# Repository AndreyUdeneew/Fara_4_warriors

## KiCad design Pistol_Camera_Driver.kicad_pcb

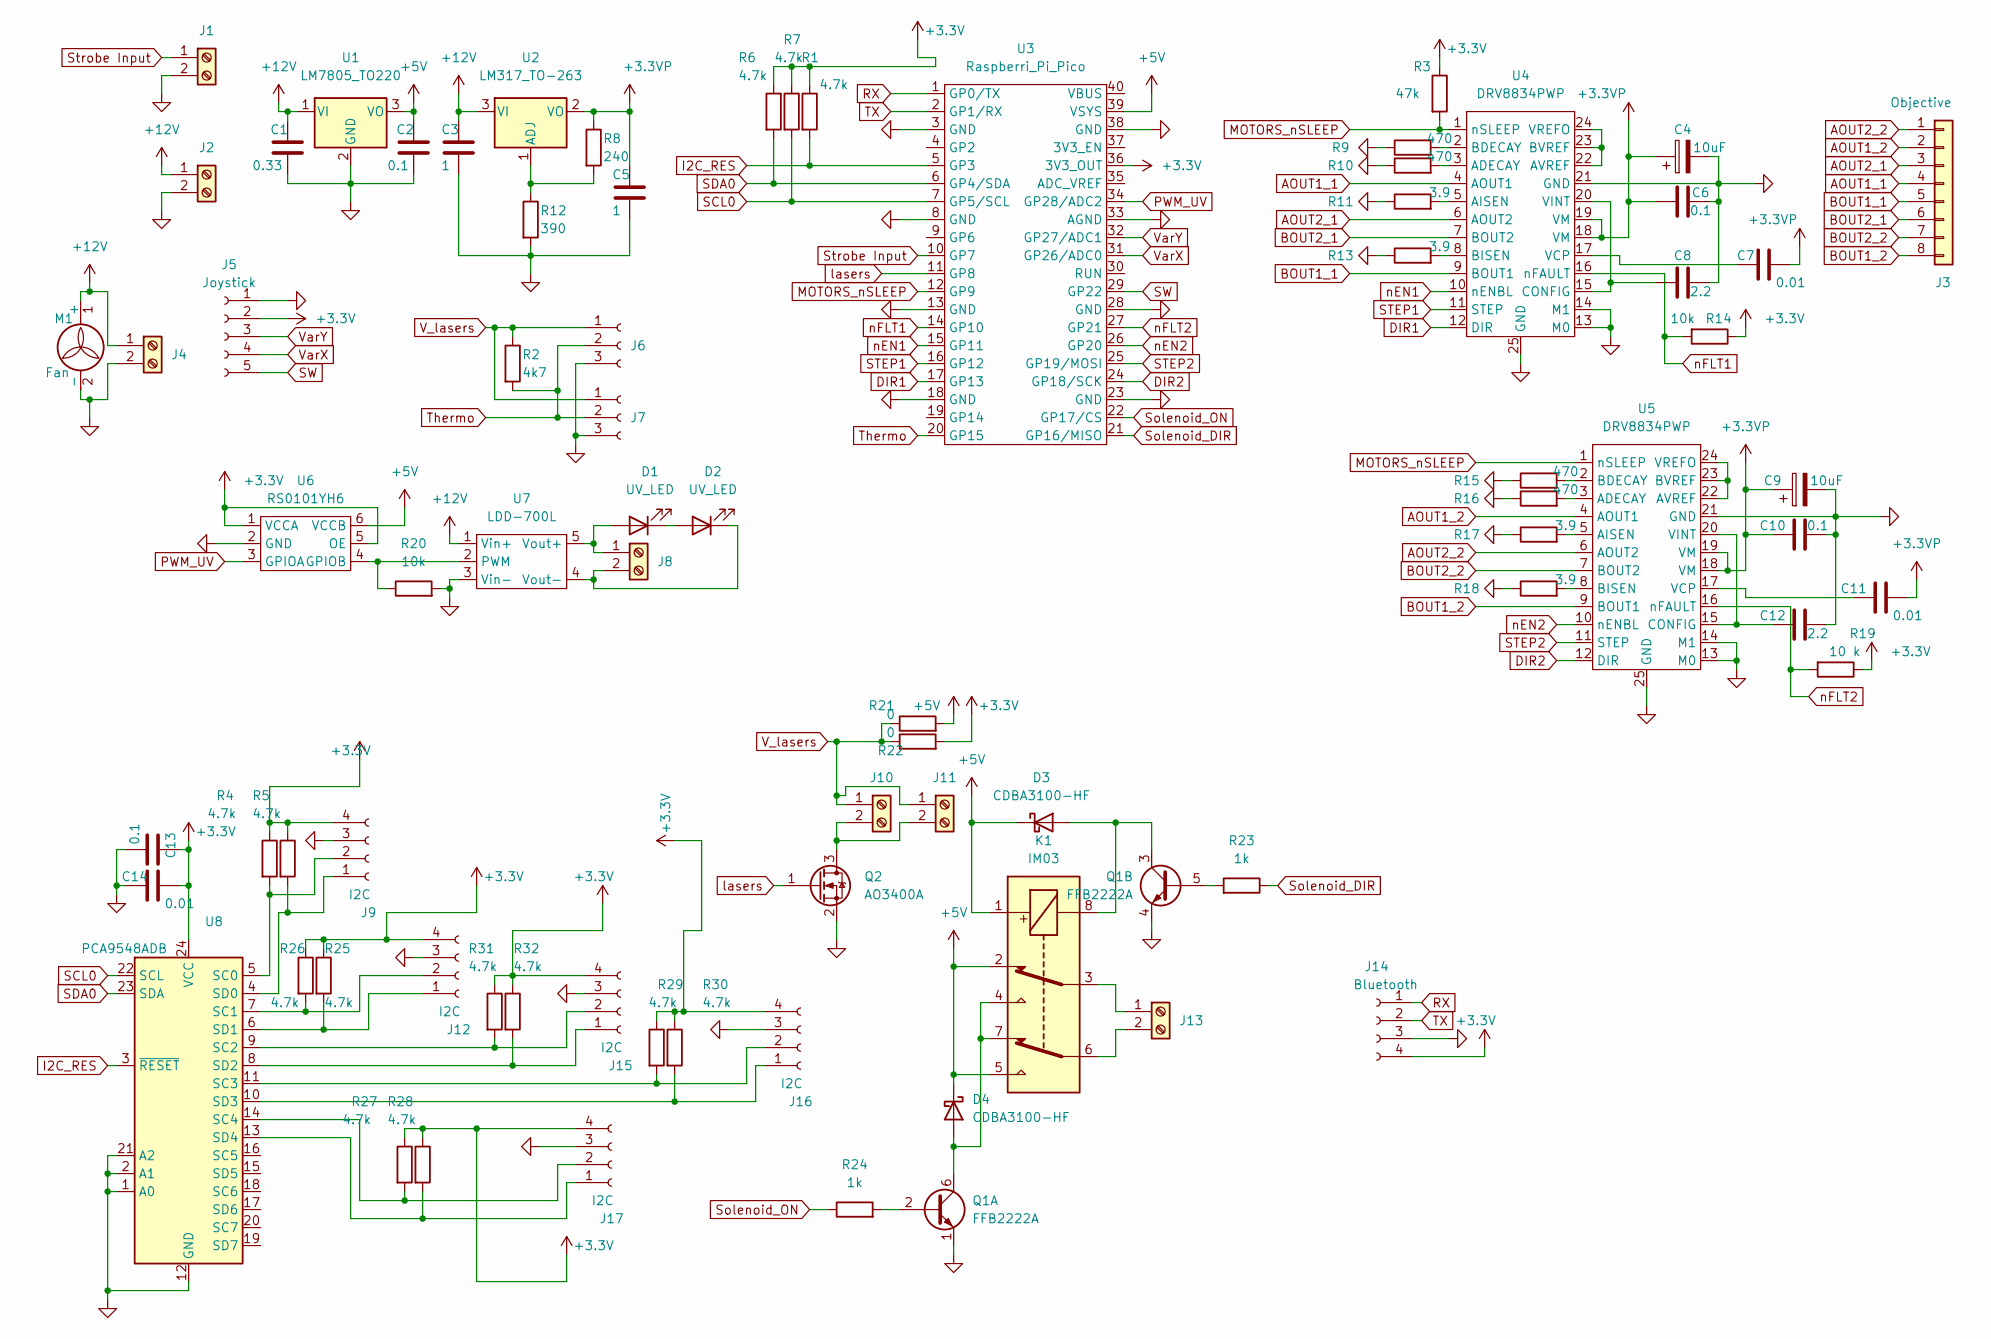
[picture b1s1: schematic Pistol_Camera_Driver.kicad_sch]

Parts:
C1: 0.33; C_0603_1608Metric_Pad1.08x0.95mm_HandSolder
C2, C6, C10, C13: 0.1; C_0603_1608Metric_Pad1.08x0.95mm_HandSolder
C3, C5: 1; C_0603_1608Metric_Pad1.08x0.95mm_HandSolder
C4, C9: 10uF; CP_Radial_D6.3mm_P2.50mm
C7, C11, C14: 0.01; C_0603_1608Metric_Pad1.08x0.95mm_HandSolder
C8, C12: 2.2; C_0603_1608Metric_Pad1.08x0.95mm_HandSolder
D1, D2: UV_LED
D3, D4: CDBA3100-HF; D_SMA
J1, J2, J4, J8, J10, J11: Screw_Terminal_01x02; PinSocket_1x02_P2.54mm_Vertical
J3: Objective; PinSocket_1x08_P1.27mm_Vertical
J5: Joystick; PinSocket_1x05_P2.54mm_Vertical
J6, J7: Conn_01x03_Socket; PinSocket_1x03_P2.54mm_Vertical
J9, J12, J15, J16, J17: I2C; PinSocket_1x04_P2.54mm_Vertical
J13: Screw_Terminal_01x02; PinSocket_1x02_P1.27mm_Vertical
J14: Bluetooth; PinSocket_1x04_P2.54mm_Vertical
K1: IM03; Relay_DPDT_AXICOM_IMSeries_Pitch5.08mm
M1: Fan
Q1: FFB2222A; SOT-363_SC-70-6_Handsoldering
Q2: AO3400A; SOT-23
R1, R4, R5, R6, R7, R25, R26, R27, R28, R29, R30, R31, R32: 4.7k; R_0603_1608Metric_Pad0.98x0.95mm_HandSolder
R2: 4k7; R_0603_1608Metric_Pad0.98x0.95mm_HandSolder
R3: 47k; R_0603_1608Metric_Pad0.98x0.95mm_HandSolder
R8: 240; R_0603_1608Metric_Pad0.98x0.95mm_HandSolder
R9, R10, R15, R16: 470; R_0603_1608Metric_Pad0.98x0.95mm_HandSolder
R11, R13, R17, R18: 3.9; R_0603_1608Metric_Pad0.98x0.95mm_HandSolder
R12: 390; R_0603_1608Metric_Pad0.98x0.95mm_HandSolder
R14, R20: 10k; R_0603_1608Metric_Pad0.98x0.95mm_HandSolder
R19: 10 k; R_0603_1608Metric_Pad0.98x0.95mm_HandSolder
R21, R22: 0; R_0603_1608Metric_Pad0.98x0.95mm_HandSolder
R23, R24: 1k; R_0603_1608Metric_Pad0.98x0.95mm_HandSolder
U1: LM7805_TO220; TO-220-3_Vertical
U2: LM317_TO-263; TO-263-2
U3: Raspberri_Pi_Pico; Raspberry Pi Pico
U4, U5: DRV8834PWP
U6: RS0101YH6; SOT-23-6_Handsoldering
U7: LDD-700L
U8: PCA9548ADB; SSOP-24_5.3x8.2mm_P0.65mm

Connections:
+3.3VP: C4.1, C5.1, C6.2, C7.2, C9.1, C10.1, C11.2, R8.1, U2.2 (VO), U4.18 (VM), U4.19 (VM), U5.18 (VM), U5.19 (VM)
+3V3: C13.1, C14.2, J5.2, J9.4, J12.4, J14.4, J15.4, J16.4, J17.4, R1.1, R3.1, R4.1, R5.1, R6.1, R7.1, R14.1, R19.1, R22.2, R25.1, R26.1, R27.1, R28.1, R29.1, R30.1, R31.1, R32.1, U3.36 (3V3_OUT), U6.1 (VCCA), U6.5 (OE), U8.24 (VCC)
+5V: C2.1, D3.1 (K), D4.1 (K), K1.1, K1.2, K1.5, R21.2, U1.3 (VO), U3.39 (VSYS), U6.6 (VCCB)
+12V: C1.1, C3.1, J2.1, J4.1, M1.1 (+), U1.1 (VI), U2.3 (VI), U7.1 (Vin+)
AOUT1_1: J3.4, U4.4 (AOUT1)
AOUT1_2: J3.2, U5.4 (AOUT1)
AOUT2_1: J3.3, U4.6 (AOUT2)
AOUT2_2: J3.1, U5.6 (AOUT2)
BOUT1_1: J3.5, U4.9 (BOUT1)
BOUT1_2: J3.8, U5.9 (BOUT1)
BOUT2_1: J3.6, U4.7 (BOUT2)
BOUT2_2: J3.7, U5.7 (BOUT2)
DIR1: U3.17 (GP13), U4.12 (DIR)
DIR2: U3.24 (GP18/SCK), U5.12 (DIR)
GND: C1.2, C2.2, C3.2, C4.2, C5.2, C6.1, C8.2, C9.2, C10.2, C12.2, C13.2, C14.1, J1.2, J2.2, J4.2, J5.1, J6.3, J7.3, J9.3, J12.3, J14.3, J15.3, J16.3, J17.3, M1.2 (-), Q1.1 (E1), Q1.4 (E2), Q2.2 (S), R9.1, R10.1, R11.1, R12.2, R13.1, R15.1, R16.1, R17.1, R18.1, R20.2, U1.2 (GND), U3.3 (GND), U3.8 (GND), U3.13 (GND), U3.18 (GND), U3.23 (GND), U3.28 (GND), U3.33 (AGND), U3.38 (GND), U4.13 (M0), U4.14 (M1), U4.21 (GND), U4.25 (GND), U5.13 (M0), U5.14 (M1), U5.21 (GND), U5.25 (GND), U6.2 (GND), U7.3 (Vin-), U8.1 (A0), U8.2 (A1), U8.12 (GND), U8.21 (A2)
I2C_RES: R1.2, U3.5 (GP3), U8.3 (~RESET)
MOTORS_nSLEEP: R3.2, U3.12 (GP9), U4.1 (nSLEEP), U5.1 (nSLEEP)
unnamed: D1.1 (K), D2.2 (A)
unnamed: D3.2 (A), K1.8, Q1.3 (C2)
unnamed: D4.2 (A), K1.4, K1.7, Q1.6 (C1)
unnamed: D1.2 (A), J8.1, U7.5 (Vout+)
unnamed: D2.1 (K), J8.2, U7.4 (Vout-)
unnamed: J9.1, R5.2, U8.4 (SD0)
unnamed: J9.2, R4.2, U8.5 (SC0)
unnamed: J10.2, J11.2, Q2.3 (D)
unnamed: J12.1, R26.2, U8.6 (SD1)
unnamed: J12.2, R25.2, U8.7 (SC1)
unnamed: J13.1, K1.3
unnamed: J13.2, K1.6
unnamed: J15.1, R32.2, U8.8 (SD2)
unnamed: J15.2, R31.2, U8.9 (SC2)
unnamed: J16.1, R30.2, U8.10 (SD3)
unnamed: J16.2, R29.2, U8.11 (SC3)
unnamed: J17.1, R28.2, U8.13 (SD4)
unnamed: J17.2, R27.2, U8.14 (SC4)
unnamed: Q1.2 (B1), R24.2
unnamed: Q1.5 (B2), R23.2
unnamed: R8.2, R12.1, U2.1 (ADJ)
unnamed: R10.2, U4.3 (ADECAY)
unnamed: R11.2, U4.5 (AISEN)
unnamed: U4.22 (AVREF), U4.23 (BVREF), U4.24 (VREFO)
unnamed: R9.2, U4.2 (BDECAY)
unnamed: R13.2, U4.8 (BISEN)
unnamed: C8.1, U4.15 (CONFIG), U4.20 (VINT)
unnamed: C7.1, U4.17 (VCP)
unnamed: R16.2, U5.3 (ADECAY)
unnamed: R17.2, U5.5 (AISEN)
unnamed: U5.22 (AVREF), U5.23 (BVREF), U5.24 (VREFO)
unnamed: R15.2, U5.2 (BDECAY)
unnamed: R18.2, U5.8 (BISEN)
unnamed: C12.1, U5.15 (CONFIG), U5.20 (VINT)
unnamed: C11.1, U5.17 (VCP)
unnamed: R20.1, U6.4 (GPIOB), U7.2 (PWM)
PWM_UV: U3.34 (GP28/ADC2), U6.3 (GPIOA)
RX: J14.1, U3.1 (GP0/TX)
SCL0: R7.2, U3.7 (GP5/SCL), U8.22 (SCL)
SDA0: R6.2, U3.6 (GP4/SDA), U8.23 (SDA)
STEP1: U3.16 (GP12), U4.11 (STEP)
STEP2: U3.25 (GP19/MOSI), U5.11 (STEP)
SW: J5.5, U3.29 (GP22)
Solenoid_DIR: R23.1, U3.21 (GP16/MISO)
Solenoid_ON: R24.1, U3.22 (GP17/CS)
Strobe Input: J1.1, U3.10 (GP7)
TX: J14.2, U3.2 (GP1/RX)
Thermo: J6.2, J7.2, R2.2, U3.20 (GP15)
V_lasers: J6.1, J7.1, J10.1, J11.1, R2.1, R21.1, R22.1
VarX: J5.4, U3.31 (GP26/ADC0)
VarY: J5.3, U3.32 (GP27/ADC1)
lasers: Q2.1 (G), U3.11 (GP8)
nEN1: U3.15 (GP11), U4.10 (nENBL)
nEN2: U3.26 (GP20), U5.10 (nENBL)
nFLT1: R14.2, U3.14 (GP10), U4.16 (nFAULT)
nFLT2: R19.2, U3.27 (GP21), U5.16 (nFAULT)

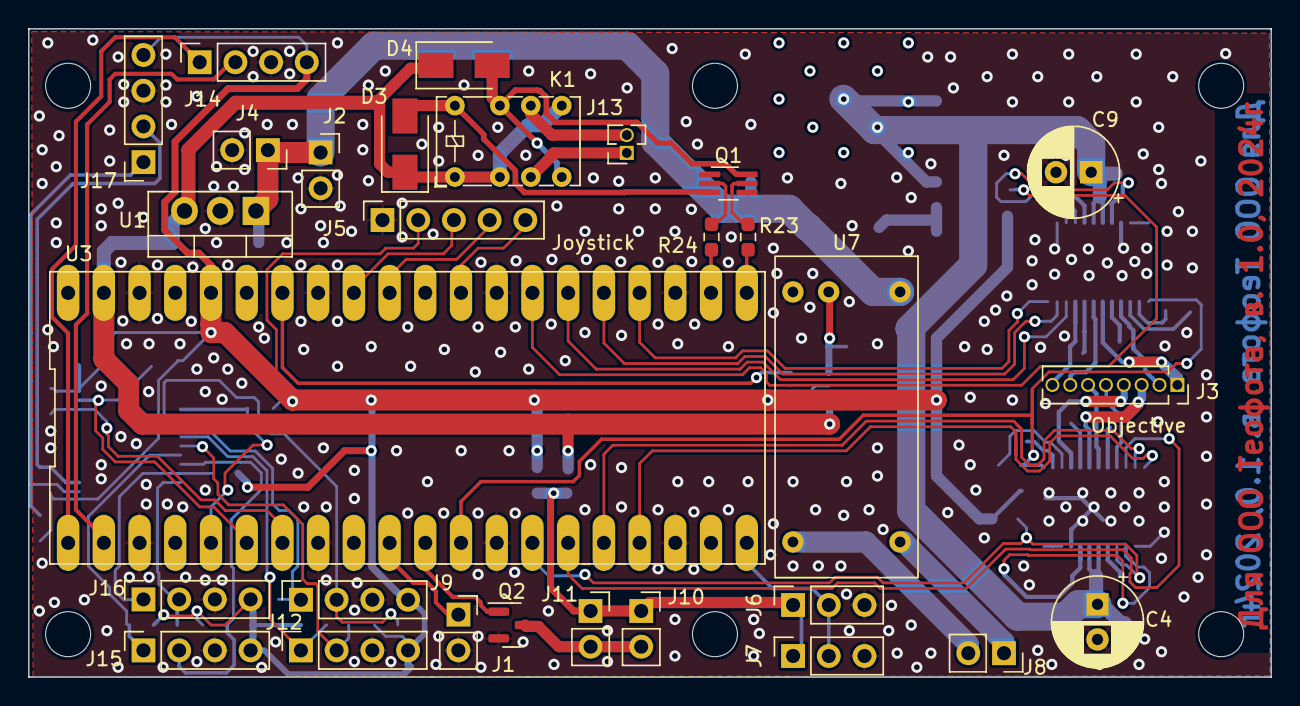
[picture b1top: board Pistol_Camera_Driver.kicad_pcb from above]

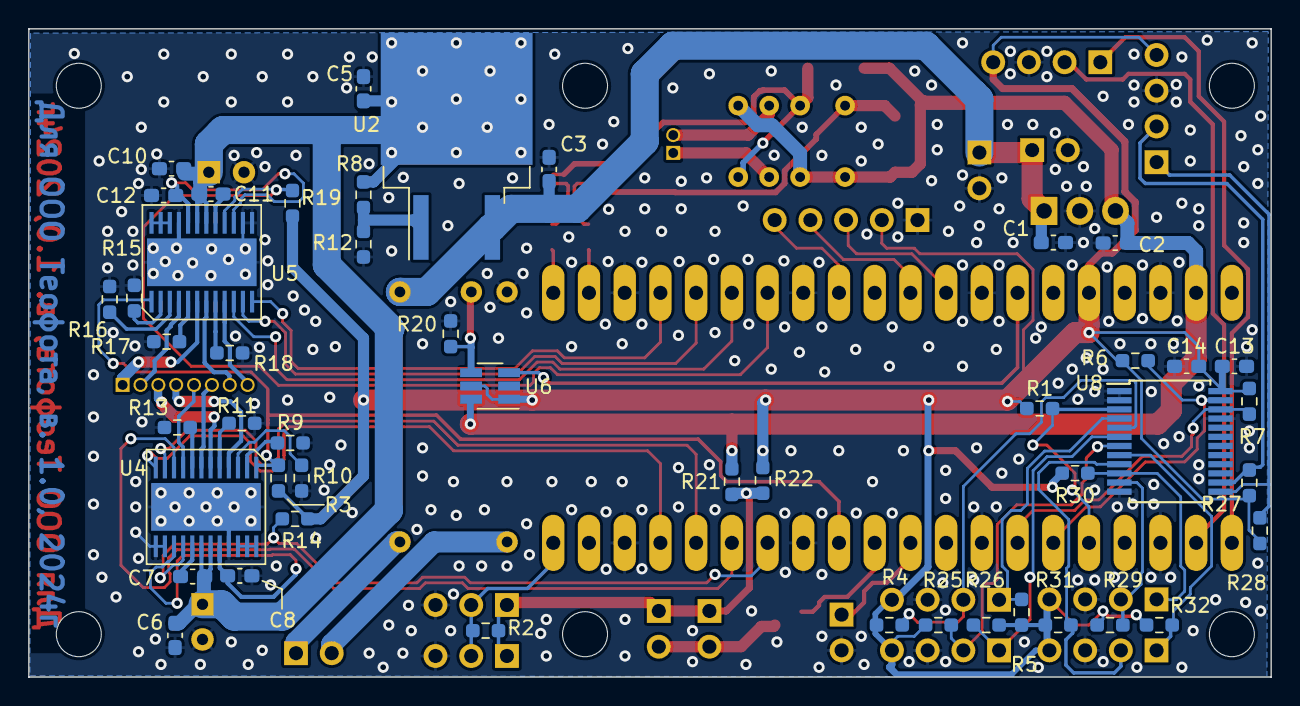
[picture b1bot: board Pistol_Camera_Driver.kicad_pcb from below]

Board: 2 copper layers, 88.3 x 46.1 mm, 76 parts (47 on the bottom side), 72 nets.

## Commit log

2024-02-05 v0.1 Circuit was completed, PCB in progress
2024-02-05 v0.2 DRC passed
2024-02-06 v0.3 Seems 2B ready
2024-02-06 v0.4 5th I2C connector was added. Seems 2B ready.
2024-04-11 v0.5 I2C multiplexer, 5 I2C cnnectors, dirty routing
2024-04-17 v0.6 thermal sensors, led strips, i2c Multiplexer were added. Ordered!
